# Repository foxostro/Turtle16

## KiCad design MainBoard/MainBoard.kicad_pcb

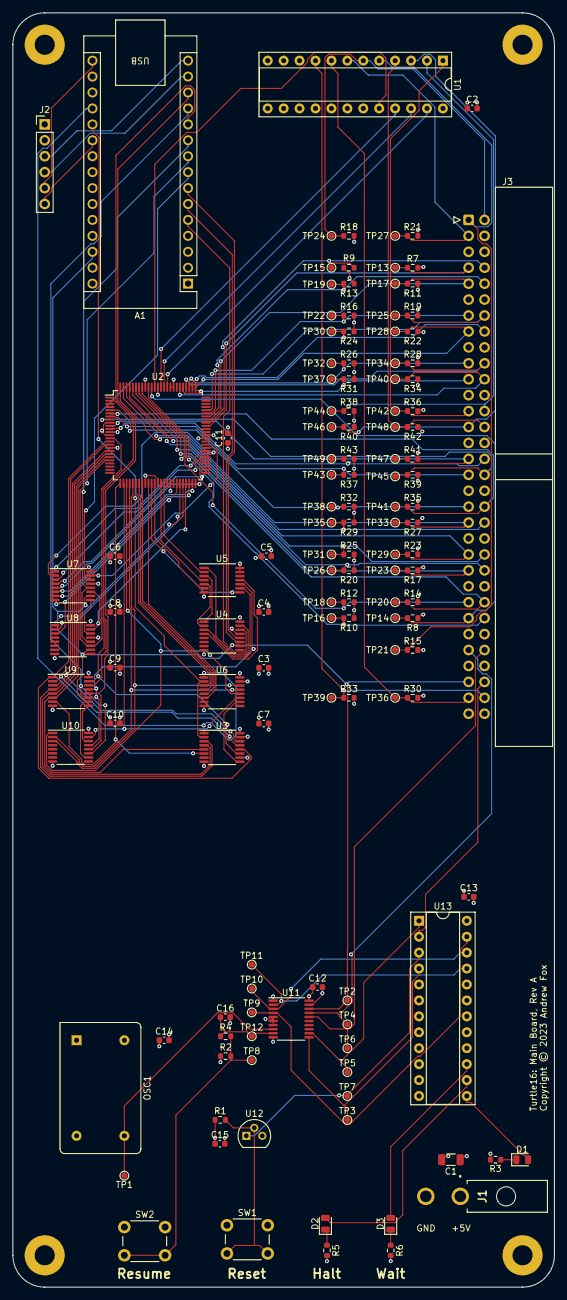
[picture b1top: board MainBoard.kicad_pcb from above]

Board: 4 copper layers, 86.4 x 203.2 mm, 135 parts (0 on the bottom side), 119 nets.

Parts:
A1: Arduino_Nano_Every; Arduino_Nano
C1: 100uF; C_1206_3216Metric
C2, C3, C4, C5, C6, C7, C8, C9, C10, C11, C12, C13, C14, C15: 0.1uF; C_0603_1608Metric
C16: 1uF; C_0603_1608Metric
D1: Power OK; LED_0805_2012Metric
D2: Halt; LED_0805_2012Metric
D3: Wait; LED_0805_2012Metric
H1, H2, H3, H4: MountingHole_Pad; MountingHole_3.2mm_M3_Pad
J1: Power In; 172448-0002
J2: SDCard Header; PinHeader_1x06_P2.54mm_Vertical
J3: 71922-164LF; IDC-Header_2x32_P2.54mm_Horizontal
OSC1: 25.175 MHz; Oscillator_DIP-14
R1, R4: 1K; R_0603_1608Metric
R2, R7, R8, R9, R10, R11, R12, R13, R14, R15, R16, R17, R18, R19, R20, R21, R22, R23, R24, R25, R26, R27, R28, R29, R30, R31, R32, R33, R34, R35, R36, R37, R38, R39, R40, R41, R42, R43: 10K; R_0603_1608Metric
R3, R5, R6: 270R; R_0603_1608Metric
SW1: Reset; SW_PUSH_6mm_H5mm
SW2: Resume; SW_PUSH_6mm_H5mm
TP1: RawClock; TestPoint_Pad_D1.0mm
TP2: ~{RST}; TestPoint_Pad_D1.0mm
TP3: Debounced; TestPoint_Pad_D1.0mm
TP4: Phi2; TestPoint_Pad_D1.0mm
TP5: Phi0; TestPoint_Pad_D1.0mm
TP6: Phi1; TestPoint_Pad_D1.0mm
TP7: ~{RST_async}; TestPoint_Pad_D1.0mm
TP8: Resume; TestPoint_Pad_D1.0mm
TP9: TestPoint_Pad_D1.0mm
TP10, TP11, TP12: TP; TestPoint_Pad_D1.0mm
TP13: Addr0; TestPoint_Pad_D1.0mm
TP14: IO0; TestPoint_Pad_D1.0mm
TP15: Addr1; TestPoint_Pad_D1.0mm
TP16: IO1; TestPoint_Pad_D1.0mm
TP17: Addr2; TestPoint_Pad_D1.0mm
TP18: IO2; TestPoint_Pad_D1.0mm
TP19: Addr3; TestPoint_Pad_D1.0mm
TP20: IO3; TestPoint_Pad_D1.0mm
TP21: Bank0; TestPoint_Pad_D1.0mm
TP22: Addr4; TestPoint_Pad_D1.0mm
TP23: IO4; TestPoint_Pad_D1.0mm
TP24: Bank1; TestPoint_Pad_D1.0mm
TP25: Addr5; TestPoint_Pad_D1.0mm
TP26: IO5; TestPoint_Pad_D1.0mm
TP27: Bank2; TestPoint_Pad_D1.0mm
TP28: Addr6; TestPoint_Pad_D1.0mm
TP29: IO6; TestPoint_Pad_D1.0mm
TP30: Addr7; TestPoint_Pad_D1.0mm
TP31: IO7; TestPoint_Pad_D1.0mm
TP32: Addr8; TestPoint_Pad_D1.0mm
TP33: IO8; TestPoint_Pad_D1.0mm
TP34: Addr9; TestPoint_Pad_D1.0mm
TP35: IO9; TestPoint_Pad_D1.0mm
TP36: ~{MemStore}; TestPoint_Pad_D1.0mm
TP37: Addr10; TestPoint_Pad_D1.0mm
TP38: IO10; TestPoint_Pad_D1.0mm
TP39: ~{MemLoad}; TestPoint_Pad_D1.0mm
TP40: Addr11; TestPoint_Pad_D1.0mm
TP41: IO11; TestPoint_Pad_D1.0mm
TP42: Addr12; TestPoint_Pad_D1.0mm
TP43: IO12; TestPoint_Pad_D1.0mm
TP44: Addr13; TestPoint_Pad_D1.0mm
TP45: IO13; TestPoint_Pad_D1.0mm
TP46: Addr14; TestPoint_Pad_D1.0mm
TP47: IO14; TestPoint_Pad_D1.0mm
TP48: Addr15; TestPoint_Pad_D1.0mm
TP49: IO15; TestPoint_Pad_D1.0mm
U1, U13: ATF22V10C; DIP-24_W7.62mm_Socket
U2: IDT7024L15PFG; TQFP-100_14x14mm_P0.5mm
U3, U6: 74HC165; TSSOP-16_4.4x5mm_P0.65mm
U4, U7, U8, U9, U10: 74HC595; TSSOP-16_4.4x5mm_P0.65mm
U5: 74AHCT04; TSSOP-14_4.4x5mm_P0.65mm
U11: 74AHCT245; TSSOP-20_4.4x6.5mm_P0.65mm
U12: MCP100-450D; TO-92

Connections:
/ArduinoInterface/CS: A1.21 (A2), J2.6
/ArduinoInterface/MISO: A1.15 (MISO), J2.3
/ArduinoInterface/MOSI: A1.14 (MOSI), J2.4
/ArduinoInterface/RAddr0: U2.59 (A0R), U7.15 (QA)
/ArduinoInterface/RAddr1: U2.58 (A1R), U7.1 (QB)
/ArduinoInterface/RAddr2: U2.57 (A2R), U7.2 (QC)
/ArduinoInterface/RAddr3: U2.56 (A3R), U7.3 (QD)
/ArduinoInterface/RAddr4: U2.55 (A4R), U7.4 (QE)
/ArduinoInterface/RAddr5: U2.50 (A5R), U7.5 (QF)
/ArduinoInterface/RAddr6: U2.49 (A6R), U7.6 (QG)
/ArduinoInterface/RAddr7: U2.48 (A7R), U7.7 (QH)
/ArduinoInterface/RAddr8: U2.47 (A8R), U8.15 (QA)
/ArduinoInterface/RAddr9: U2.46 (A9R), U8.1 (QB)
/ArduinoInterface/RAddr10: U2.45 (A10R), U8.2 (QC)
/ArduinoInterface/RAddr11: U2.44 (A11R), U8.3 (QD)
/ArduinoInterface/RCLKa: A1.7 (D4), U4.12 (RCLK)
/ArduinoInterface/RCLKb: A1.10 (D7), U7.12 (RCLK), U8.12 (RCLK)
/ArduinoInterface/RCLKc: A1.13 (D10), U9.12 (RCLK), U10.12 (RCLK)
/ArduinoInterface/RIO0: U2.14 (I/O0R), U3.11 (D0), U9.15 (QA)
/ArduinoInterface/RIO1: U2.15 (I/O1R), U3.12 (D1), U9.1 (QB)
/ArduinoInterface/RIO2: U2.16 (I/O2R), U3.13 (D2), U9.2 (QC)
/ArduinoInterface/RIO3: U2.18 (I/O3R), U3.14 (D3), U9.3 (QD)
/ArduinoInterface/RIO4: U2.19 (I/O4R), U3.3 (D4), U9.4 (QE)
/ArduinoInterface/RIO5: U2.20 (I/O5R), U3.4 (D5), U9.5 (QF)
/ArduinoInterface/RIO6: U2.21 (I/O6R), U3.5 (D6), U9.6 (QG)
/ArduinoInterface/RIO7: U2.26 (I/O7R), U3.6 (D7), U9.7 (QH)
/ArduinoInterface/RIO8: U2.27 (I/O8R), U6.11 (D0), U10.15 (QA)
/ArduinoInterface/RIO9: U2.28 (I/O9R), U6.12 (D1), U10.1 (QB)
/ArduinoInterface/RIO10: U2.29 (I/O10R), U6.13 (D2), U10.2 (QC)
/ArduinoInterface/RIO11: U2.30 (I/O11R), U6.14 (D3), U10.3 (QD)
/ArduinoInterface/RIO12: U2.31 (I/O12R), U6.3 (D4)
/ArduinoInterface/RIO13: U2.32 (I/O13R), U6.4 (D5)
/ArduinoInterface/RIO14: U2.33 (I/O14R), U6.5 (D6)
/ArduinoInterface/RIO15: U2.35 (I/O15R), U6.6 (D7)
/ArduinoInterface/R/~WR: U2.37 (R/~WR), U5.6
/ArduinoInterface/SCK: A1.16 (SCK), J2.5
/ArduinoInterface/SCKa: A1.6 (D3), U4.11 (SRCLK)
/ArduinoInterface/SCKb: A1.9 (D6), U7.11 (SRCLK), U8.11 (SRCLK)
/ArduinoInterface/SCKc: A1.12 (D9), U9.11 (SRCLK), U10.11 (SRCLK)
/ArduinoInterface/SCKd: A1.20 (A1), U3.2 (CP), U6.2 (CP)
/ArduinoInterface/SIa: A1.5 (D2), U4.14 (SER)
/ArduinoInterface/SIb: A1.8 (D5), U7.14 (SER)
/ArduinoInterface/SIc: A1.11 (D8), U9.14 (SER)
/ArduinoInterface/~CER: U2.40 (~CER), U5.2
/ArduinoInterface/~DataOut: U5.10, U9.13 (~OE), U10.13 (~OE)
/ArduinoInterface/~OER: U2.36 (~OER), U5.8
/ArduinoInterface/~PL: A1.19 (A0), U3.1 (~PL), U6.1 (~PL)
/ArduinoInterface/~SEMR: U2.39 (~SEMR), U5.4
/Clock/Button0: TP3.1, U11.11 (B7), U13.4 (IN)
/Clock/ButtonRC: C16.1, R4.1, TP12.1, U11.9 (A7)
/Clock/HaltLED: D2.2 (A), U13.14 (I/O)
/Clock/Phi0: TP5.1, U11.12 (B6), U13.1 (IN/CLK)
/Clock/Phi1: J3.56, TP6.1, U11.16 (B2)
/Clock/Phi1_0: TP9.1, U11.4 (A2), U13.23 (I/O)
/Clock/Phi2: J3.55, TP4.1, U11.17 (B1)
/Clock/Phi2_0: TP10.1, U11.3 (A1), U13.22 (I/O)
/Clock/PowerLED: D1.2 (A), U13.13 (IN/~OE)
/Clock/RawClock: OSC1.8 (OUT), TP1.1, U11.8 (A6)
/Clock/WaitLED: D3.2 (A), U13.15 (I/O)
/Clock//RST_sync0: TP11.1, U11.2 (A0), U13.21 (I/O)
/Clock/~RST_async: TP7.1, U12.1 (~RST), U13.3 (IN)
/RAM/Addr0: J3.7, R7.1, TP13.1, U2.66 (A0L)
/RAM/Addr1: J3.8, R9.1, TP15.1, U2.67 (A1L)
/RAM/Addr2: J3.9, R11.1, TP17.1, U2.68 (A2L)
/RAM/Addr3: J3.10, R13.1, TP19.1, U2.69 (A3L)
/RAM/Addr4: J3.13, R16.1, TP22.1, U2.70 (A4L)
/RAM/Addr5: J3.14, R19.1, TP25.1, U2.71 (A5L)
/RAM/Addr6: J3.15, R22.1, TP28.1, U2.76 (A6L)
/RAM/Addr7: J3.16, R24.1, TP30.1, U2.77 (A7L)
/RAM/Addr8: J3.19, R26.1, TP32.1, U2.78 (A8L)
/RAM/Addr9: J3.20, R28.1, TP34.1, U2.79 (A9L)
/RAM/Addr10: J3.21, R31.1, TP37.1, U2.80 (A10L)
/RAM/Addr11: J3.22, R34.1, TP40.1, U2.81 (A11L)
/RAM/Addr12: J3.25, R36.1, TP42.1, U1.1 (IN/CLK)
/RAM/Addr13: J3.26, R38.1, TP44.1, U1.2 (IN)
/RAM/Addr14: J3.27, R40.1, TP46.1, U1.3 (IN)
/RAM/Addr15: J3.28, R42.1, TP48.1, U1.4 (IN)
/RAM/Bank0: J3.1, R15.1, TP21.1, U1.5 (IN)
/RAM/Bank1: J3.2, R18.1, TP24.1, U1.6 (IN)
/RAM/Bank2: J3.3, R21.1, TP27.1, U1.7 (IN)
/RAM/IO0: J3.51, R8.1, TP14.1, U2.90 (I/O0L)
/RAM/IO1: J3.52, R10.1, TP16.1, U2.91 (I/O1L)
/RAM/IO2: J3.49, R12.1, TP18.1, U2.93 (I/O2L)
/RAM/IO3: J3.50, R14.1, TP20.1, U2.94 (I/O3L)
/RAM/IO4: J3.45, R17.1, TP23.1, U2.95 (I/O4L)
/RAM/IO5: J3.46, R20.1, TP26.1, U2.96 (I/O5L)
/RAM/IO6: J3.43, R23.1, TP29.1, U2.97 (I/O6L)
/RAM/IO7: J3.44, R25.1, TP31.1, U2.98 (I/O7L)
/RAM/IO8: J3.39, R27.1, TP33.1, U2.99 (I/O8L)
/RAM/IO9: J3.40, R29.1, TP35.1, U2.100 (I/O9L)
/RAM/IO10: J3.37, R32.1, TP38.1, U2.5 (I/O10L)
/RAM/IO11: J3.38, R35.1, TP41.1, U2.6 (I/O11L)
/RAM/IO12: J3.33, R37.1, TP43.1, U2.7 (I/O12L)
/RAM/IO13: J3.34, R39.1, TP45.1, U2.8 (I/O13L)
/RAM/IO14: J3.31, R41.1, TP47.1, U2.10 (I/O14L)
/RAM/IO15: J3.32, R43.1, TP49.1, U2.11 (I/O15L)
/RAM/R/~WL: U1.21 (I/O), U2.87 (R/~WL)
/RAM/~CEL: U1.23 (I/O), U2.85 (~CEL)
/RAM/~MemLoad: J3.62, R33.1, TP39.1, U1.9 (IN)
/RAM/~MemStore: J3.61, R30.1, TP36.1, U1.8 (IN)
/RAM/~OEL: U1.20 (I/O), U2.89 (~OEL)
/RAM/~SEML: U1.22 (I/O), U2.86 (~SEML)
/~HLT: J3.60, U13.2 (IN)
/~RST: A1.3 (~RESET), A1.28 (~RESET), J3.59, TP2.1, U4.10 (~SRCLR), U7.10 (~SRCLR), U8.10 (~SRCLR), U9.10 (~SRCLR), U10.10 (~SRCLR), U11.18 (B0)
GND: A1.4 (GND), A1.29 (GND), C1.2, C2.2, C3.2, C4.2, C5.2, C6.2, C7.2, C8.2, C9.2, C10.2, C11.2, C12.2, C13.2, C14.2, C15.2, C16.2, H1.1, H2.1, H3.1, H4.1, J1.2, J2.1, J3.5, J3.6, J3.11, J3.12, J3.17, J3.18, J3.23, J3.24, J3.29, J3.30, J3.35, J3.36, J3.41, J3.42, J3.47, J3.48, J3.53, J3.54, OSC1.7 (GND), R3.2, R5.2, R6.2, R7.2, R8.2, R9.2, R10.2, R11.2, R12.2, R13.2, R14.2, R15.2, R16.2, R17.2, R18.2, R19.2, R20.2, R21.2, R22.2, R23.2, R24.2, R25.2, R26.2, R27.2, R28.2, R29.2, R31.2, R32.2, R34.2, R35.2, R36.2, R37.2, R38.2, R39.2, R40.2, R41.2, R42.2, R43.2, SW1.1, SW2.1, U1.12 (GND), U2.9 (GND), U2.13 (GND), U2.34 (GND), U2.38 (GND), U2.41 (~UBR), U2.42 (~LBR), U2.63 (GND), U2.83 (~LBL), U2.84 (~UBL), U2.92 (GND), U3.8 (GND), U3.10 (DS), U3.15 (~CE), U4.8 (GND), U4.13 (~OE), U5.7 (GND), U6.8 (GND), U6.15 (~CE), U7.8 (GND), U7.13 (~OE), U8.8 (GND), U8.13 (~OE), U9.8 (GND), U10.8 (GND), U11.5 (A3), U11.6 (A4), U11.7 (A5), U11.10 (GND), U11.19 (CE), U12.3 (VSS), U13.12 (GND)
unnamed: D1.1 (K), R3.1
unnamed: D2.1 (K), R5.1
unnamed: D3.1 (K), R6.1
unnamed: R2.2, R4.2, SW2.2, TP8.1
unnamed: U3.9 (Q7), U6.10 (DS)
unnamed: U4.15 (QA), U5.1
unnamed: U4.1 (QB), U5.3
unnamed: U4.2 (QC), U5.5
unnamed: U4.3 (QD), U5.9
unnamed: U4.4 (QE), U5.11
unnamed: U7.9 (QH'), U8.14 (SER)
unnamed: U9.9 (QH'), U10.14 (SER)
unnamed: R1.2, SW1.2, U12.2 (VDD)
VCC: A1.30 (VIN), C1.1, C2.1, C3.1, C4.1, C5.1, C6.1, C7.1, C8.1, C9.1, C10.1, C11.1, C12.1, C13.1, C14.1, C15.1, J1.1, J2.2, J3.57, J3.58, J3.63, J3.64, OSC1.14 (Vcc), R1.1, R2.1, R30.2, R33.2, U1.24 (VCC), U2.12 (VCC), U2.17 (VCC), U2.62 (M/~S), U2.88 (VCC), U3.16 (VCC), U4.16 (VCC), U5.13, U5.14 (VCC), U6.16 (VCC), U7.16 (VCC), U8.16 (VCC), U9.16 (VCC), U10.16 (VCC), U11.1 (A->B), U11.20 (VCC), U13.24 (VCC)

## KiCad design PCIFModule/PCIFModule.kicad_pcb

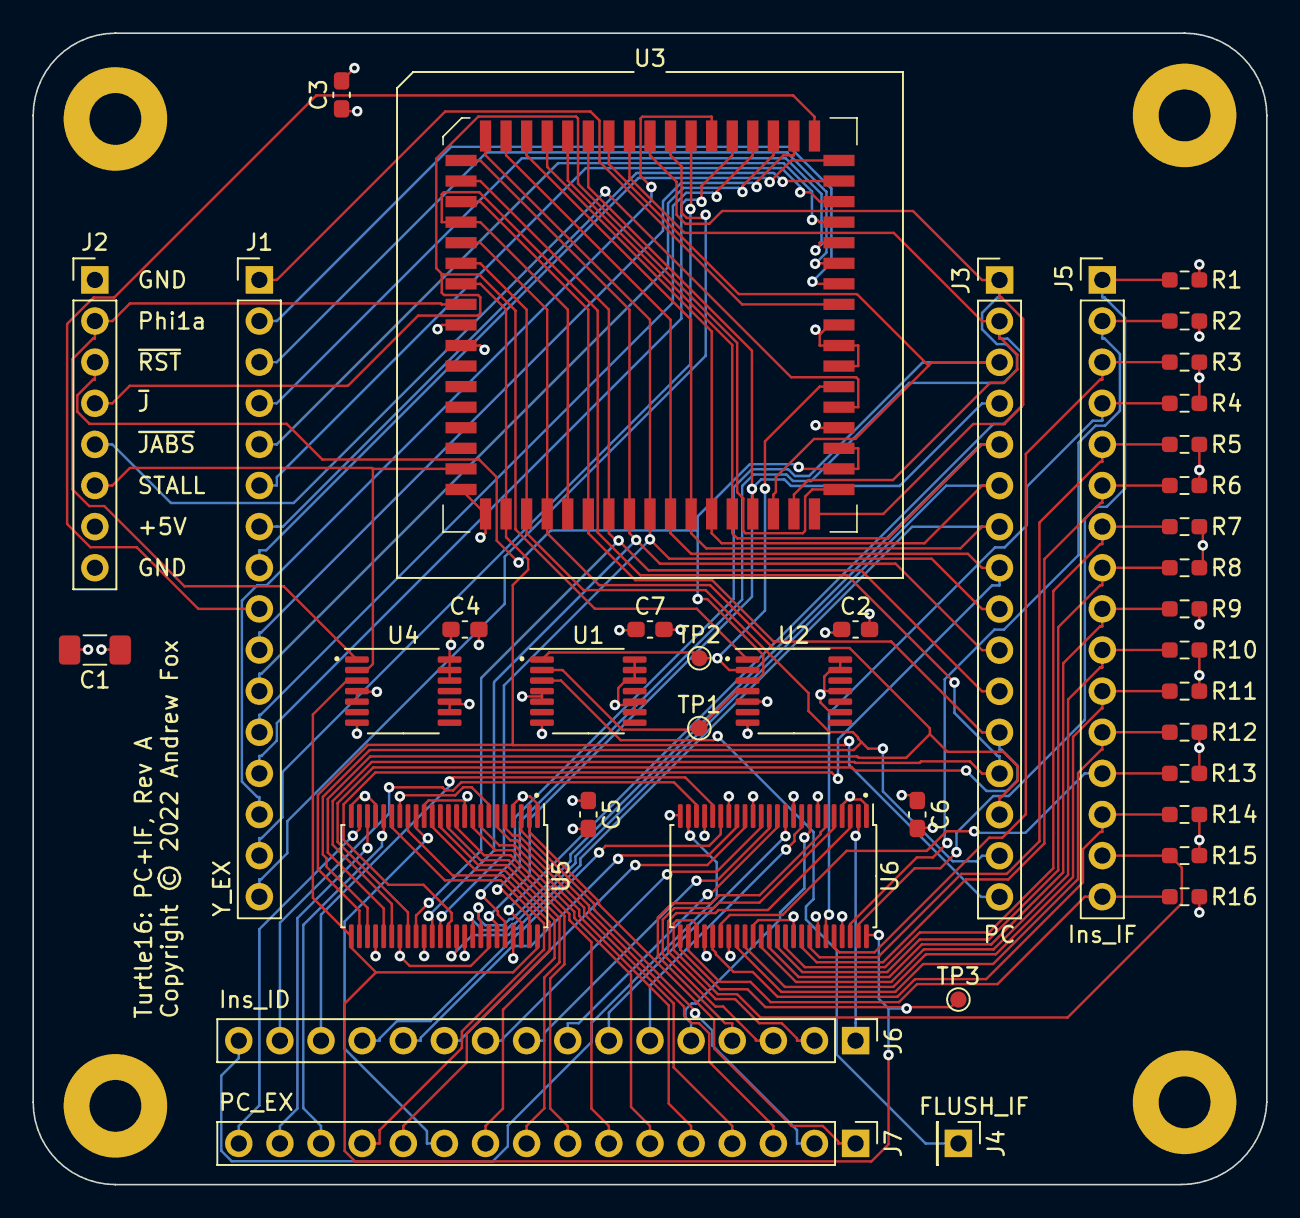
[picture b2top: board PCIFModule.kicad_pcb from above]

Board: 4 copper layers, 76.2 x 71.1 mm, 43 parts (0 on the bottom side), 91 nets.

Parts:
C1: 100µF; C_1206_3216Metric_Pad1.33x1.80mm_HandSolder
C2, C3, C4, C5, C6, C7: 100nF; C_0603_1608Metric_Pad1.08x0.95mm_HandSolder
H1, H2, H3, H4: MountingHole_Pad; MountingHole_3.2mm_M3_Pad
J1: Y_EX; PinHeader_1x16_P2.54mm_Vertical
J2: Control Signals; PinHeader_1x08_P2.54mm_Vertical
J3: PC; PinHeader_1x16_P2.54mm_Vertical
J4: FLUSH_IF; PinHeader_1x01_P2.54mm_Vertical
J5: Ins_IF; PinHeader_1x16_P2.54mm_Vertical
J6: Ins_ID; PinHeader_1x16_P2.54mm_Vertical
J7: PC_EX; PinHeader_1x16_P2.54mm_Vertical
R1, R2, R3, R4, R5, R6, R7, R8, R9, R10, R11, R12, R13, R14, R15, R16: 10K; R_0603_1608Metric_Pad0.98x0.95mm_HandSolder
TP1: TP; TestPoint_Pad_D1.0mm
TP2: RS1; TestPoint_Pad_D1.0mm
TP3: CLK; TestPoint_Pad_D1.0mm
U1, U4: 74ABT32; TSSOP-14_4.4x5mm_P0.65mm
U2: 74AHCT04; TSSOP-14_4.4x5mm_P0.65mm
U3: IDT7381; PLCC-68_SMD-Socket
U5, U6: 74ABT16374; TSSOP-48_6.1x12.5mm_P0.5mm

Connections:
/IF/FLUSH_IF: J4.1, U1.3
/IF/Ins_ID0: J6.1, U6.2 (1Q1)
/IF/Ins_ID1: J6.2, U6.3 (1Q2)
/IF/Ins_ID2: J6.3, U6.5 (1Q3)
/IF/Ins_ID3: J6.4, U6.6 (1Q4)
/IF/Ins_ID4: J6.5, U6.8 (1Q5)
/IF/Ins_ID5: J6.6, U6.9 (1Q6)
/IF/Ins_ID6: J6.7, U6.11 (1Q7)
/IF/Ins_ID7: J6.8, U6.12 (1Q8)
/IF/Ins_ID8: J6.9, U6.13 (2Q1)
/IF/Ins_ID9: J6.10, U6.14 (2Q2)
/IF/Ins_ID10: J6.11, U6.16 (2Q3)
/IF/Ins_ID11: J6.12, U6.17 (2Q4)
/IF/Ins_ID12: J6.13, U6.19 (2Q5)
/IF/Ins_ID13: J6.14, U6.20 (2Q6)
/IF/Ins_ID14: J6.15, U6.22 (2Q7)
/IF/Ins_ID15: J6.16, U6.23 (2Q8)
/IF/Ins_IF0: J5.1, R1.1, U6.47 (1D1)
/IF/Ins_IF1: J5.2, R2.1, U6.46 (1D2)
/IF/Ins_IF2: J5.3, R3.1, U6.44 (1D3)
/IF/Ins_IF3: J5.4, R4.1, U6.43 (1D4)
/IF/Ins_IF4: J5.5, R5.1, U6.41 (1D5)
/IF/Ins_IF5: J5.6, R6.1, U6.40 (1D6)
/IF/Ins_IF6: J5.7, R7.1, U6.38 (1D7)
/IF/Ins_IF7: J5.8, R8.1, U6.37 (1D8)
/IF/Ins_IF8: J5.9, R9.1, U6.36 (2D1)
/IF/Ins_IF9: J5.10, R10.1, U6.35 (2D2)
/IF/Ins_IF10: J5.11, R11.1, U6.33 (2D3)
/IF/Ins_IF11: J5.12, R12.1, U6.32 (2D4)
/IF/Ins_IF12: J5.13, R13.1, U6.30 (2D5)
/IF/Ins_IF13: J5.14, R14.1, U6.29 (2D6)
/IF/Ins_IF14: J5.15, R15.1, U6.27 (2D7)
/IF/Ins_IF15: J5.16, R16.1, U6.26 (2D8)
/IF/PC_EX0: J7.1, U5.2 (1Q1)
/IF/PC_EX1: J7.2, U5.3 (1Q2)
/IF/PC_EX2: J7.3, U5.5 (1Q3)
/IF/PC_EX3: J7.4, U5.6 (1Q4)
/IF/PC_EX4: J7.5, U5.8 (1Q5)
/IF/PC_EX5: J7.6, U5.9 (1Q6)
/IF/PC_EX6: J7.7, U5.11 (1Q7)
/IF/PC_EX7: J7.8, U5.12 (1Q8)
/IF/PC_EX8: J7.9, U5.13 (2Q1)
/IF/PC_EX9: J7.10, U5.14 (2Q2)
/IF/PC_EX10: J7.11, U5.16 (2Q3)
/IF/PC_EX11: J7.12, U5.17 (2Q4)
/IF/PC_EX12: J7.13, U5.19 (2Q5)
/IF/PC_EX13: J7.14, U5.20 (2Q6)
/IF/PC_EX14: J7.15, U5.22 (2Q7)
/IF/PC_EX15: J7.16, U5.23 (2Q8)
/IF/Phi1a: J2.2, U3.17 (CLK), U4.1
/IF/STALL: J2.6, U3.25 (~ENF), U4.2
/IF/Y_EX0: J1.1, U3.53 (B0)
/IF/Y_EX1: J1.2, U3.54 (B1)
/IF/Y_EX2: J1.3, U3.55 (B2)
/IF/Y_EX3: J1.4, U3.56 (B3)
/IF/Y_EX4: J1.5, U3.57 (B4)
/IF/Y_EX5: J1.6, U3.58 (B5)
/IF/Y_EX6: J1.7, U3.59 (B6)
/IF/Y_EX7: J1.8, U3.60 (B7)
/IF/Y_EX8: J1.9, U3.61 (B8)
/IF/Y_EX9: J1.10, U3.62 (B9)
/IF/Y_EX10: J1.11, U3.63 (B10)
/IF/Y_EX11: J1.12, U3.64 (B11)
/IF/Y_EX12: J1.13, U3.65 (B12)
/IF/Y_EX13: J1.14, U3.66 (B13)
/IF/Y_EX14: J1.15, U3.67 (B14)
/IF/Y_EX15: J1.16, U3.68 (B15)
/IF/sheet5FE3DA15/PC0: J3.1, U3.1 (A0), U3.43 (F0), U5.47 (1D1)
/IF/sheet5FE3DA15/PC1: J3.2, U3.2 (A1), U3.42 (F1), U5.46 (1D2)
/IF/sheet5FE3DA15/PC2: J3.3, U3.3 (A2), U3.41 (F2), U5.44 (1D3)
/IF/sheet5FE3DA15/PC3: J3.4, U3.4 (A3), U3.40 (F3), U5.43 (1D4)
/IF/sheet5FE3DA15/PC4: J3.5, U3.5 (A4), U3.39 (F4), U5.41 (1D5)
/IF/sheet5FE3DA15/PC5: J3.6, U3.6 (A5), U3.38 (F5), U5.40 (1D6)
/IF/sheet5FE3DA15/PC6: J3.7, U3.7 (A6), U3.37 (F6), U5.38 (1D7)
/IF/sheet5FE3DA15/PC7: J3.8, U3.8 (A7), U3.36 (F7), U5.37 (1D8)
/IF/sheet5FE3DA15/PC8: J3.9, U3.9 (A8), U3.35 (F8), U5.36 (2D1)
/IF/sheet5FE3DA15/PC9: J3.10, U3.10 (A9), U3.34 (F9), U5.35 (2D2)
/IF/sheet5FE3DA15/PC10: J3.11, U3.11 (A10), U3.33 (F10), U5.33 (2D3)
/IF/sheet5FE3DA15/PC11: J3.12, U3.12 (A11), U3.32 (F11), U5.32 (2D4)
/IF/sheet5FE3DA15/PC12: J3.13, U3.13 (A12), U3.31 (F12), U5.30 (2D5)
/IF/sheet5FE3DA15/PC13: J3.14, U3.14 (A13), U3.30 (F13), U5.29 (2D6)
/IF/sheet5FE3DA15/PC14: J3.15, U3.15 (A14), U3.29 (F14), U5.27 (2D7)
/IF/sheet5FE3DA15/PC15: J3.16, U3.16 (A15), U3.28 (F15), U5.26 (2D8)
/IF/~JABS: J2.5, U3.48 (RS0)
/IF/~J: J2.4, U2.1, U3.44 (C0)
/IF/~RST_sync: J2.3, U2.3, U3.45 (I0), U3.46 (I1)
GND: C1.2, C2.2, C3.2, C4.2, C5.2, C6.2, C7.2, H1.1, H2.1, H3.1, H4.1, J2.1, J2.8, R1.2, R2.2, R3.2, R4.2, R5.2, R6.2, R7.2, R8.2, R9.2, R10.2, R11.2, R12.2, R13.2, R14.2, R15.2, R16.2, U1.7 (GND), U2.7 (GND), U3.19 (GND), U3.26 (FTF), U3.27 (~OE), U3.47 (I2), U4.7 (GND), U5.1 (1~OE), U5.4 (GND), U5.10 (GND), U5.15 (GND), U5.21 (GND), U5.24 (2~OE), U5.28 (GND), U5.34 (GND), U5.39 (GND), U5.45 (GND), U6.1 (1~OE), U6.4 (GND), U6.10 (GND), U6.15 (GND), U6.21 (GND), U6.24 (2~OE), U6.28 (GND), U6.34 (GND), U6.39 (GND), U6.45 (GND)
unnamed: TP1.1, U1.2, U2.4
unnamed: TP2.1, U1.1, U2.2, U3.49 (RS1)
unnamed: TP3.1, U4.3, U5.25 (2CLK), U5.48 (1CLK), U6.25 (2CLK), U6.48 (1CLK)
VCC: C1.1, C2.1, C3.1, C4.1, C5.1, C6.1, C7.1, J2.7, U1.4, U1.5, U1.9, U1.10, U1.12, U1.13, U1.14 (VCC), U2.5, U2.9, U2.11, U2.13, U2.14 (VCC), U3.18 (VCC), U3.50 (FTAB), U3.51 (~ENB), U3.52 (~ENA), U4.4, U4.5, U4.9, U4.10, U4.12, U4.13, U4.14 (VCC), U5.7 (VCC), U5.18 (VCC), U5.31 (VCC), U5.42 (VCC), U6.7 (VCC), U6.18 (VCC), U6.31 (VCC), U6.42 (VCC)

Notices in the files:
MainBoard/MainBoard.kicad_pcb:
Copyright © 2023 Andrew Fox
PCIFModule/PCIFModule.kicad_pcb:
Copyright © 2022 Andrew Fox
ProgramCounterPrototype/ProgramCounterPrototype.kicad_pcb:
Copyright © 2021 Andrew Fox
